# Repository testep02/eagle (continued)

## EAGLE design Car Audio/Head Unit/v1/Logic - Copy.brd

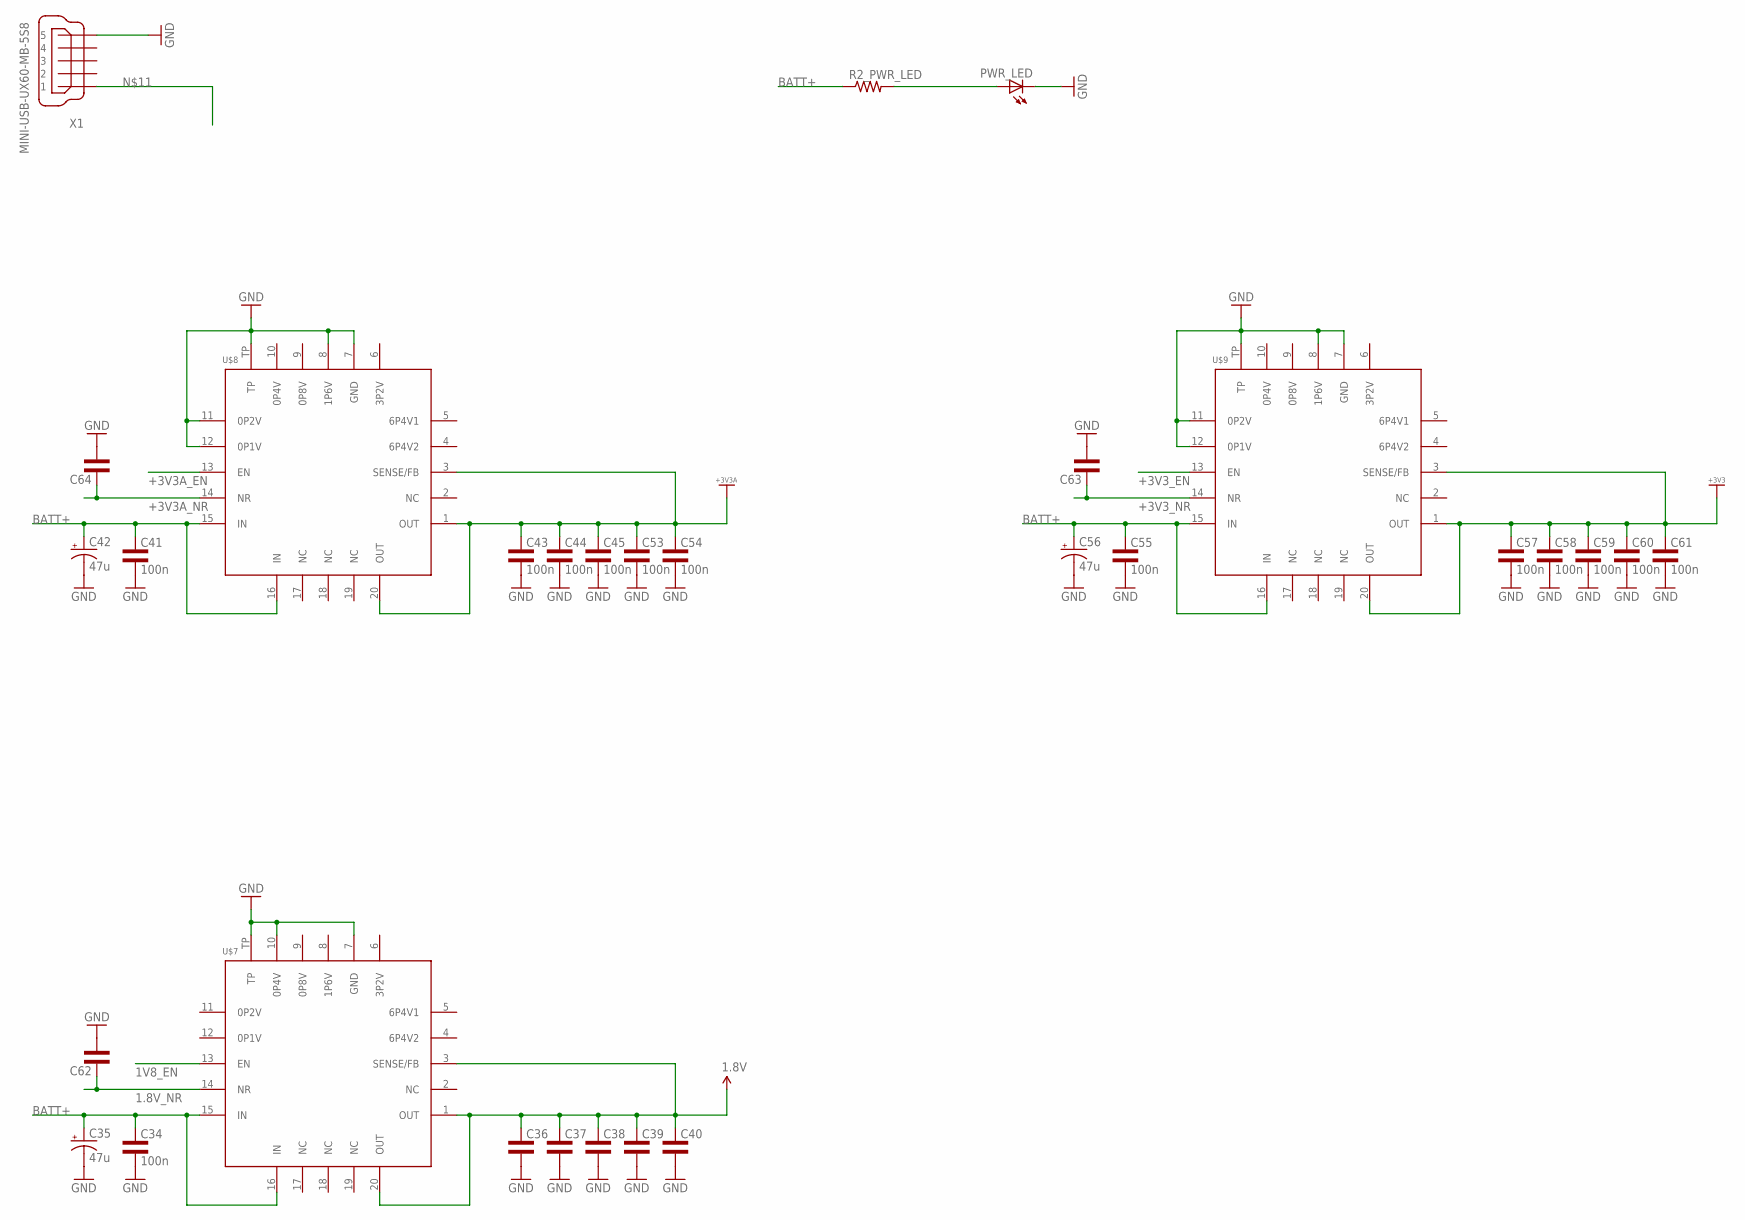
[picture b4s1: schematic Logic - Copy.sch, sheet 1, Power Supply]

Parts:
C34, C41, C43, C44, C45, C53, C54, C55, C57, C58, C59, C60, C61: 100n; 0805L3
C35, C42, C56: 47u; CT3528
C36, C37, C38, C39, C40: CAP0805L3; 0805L3
C62, C63, C64: CAP0402L3; 0402L3
PWR_LED: LEDCHIP-LED0603; CHIP-LED0603
R2_PWR_LED: RESISTOR0402-RES; 0402-RES
U$7, U$8, U$9: POWER-SUPPLY_POS_V1_TI_LDO_TPS7A4700; POWER-SUPPLY_POS_V1_TI_LDO_VQFN-20
X1: MINI-USB-UX60-MB-5S8; UX60-MB-5S8

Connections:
1.8V: C36.1, C37.1, C38.1, C39.1, C40.1, U$7.1 (OUT), U$7.3 (SENSE/FB), U$7.20 (OUT); also elsewhere on the board
1.8V_NR: C62.P$1 (1), U$7.14 (NR)
1V8_EN: U$7.13 (EN)
+3V3: C57.1, C58.1, C59.1, C60.1, C61.1, U$9.1 (OUT), U$9.3 (SENSE/FB), U$9.20 (OUT); also elsewhere on the board
+3V3A: C43.1, C44.1, C45.1, C53.1, C54.1, U$8.1 (OUT), U$8.3 (SENSE/FB), U$8.20 (OUT); also elsewhere on the board
+3V3A_EN: U$8.13 (EN)
+3V3A_NR: C64.P$1 (1), U$8.14 (NR)
+3V3_EN: U$9.13 (EN)
+3V3_NR: C63.P$1 (1), U$9.14 (NR)
BATT+: C34.1, C35.+, C41.1, C42.+, C55.1, C56.+, R2_PWR_LED.1, U$7.15 (IN), U$7.16 (IN), U$8.15 (IN), U$8.16 (IN), U$9.15 (IN), U$9.16 (IN)
GND: C34.2, C35.-, C36.2, C37.2, C38.2, C39.2, C40.2, C41.2, C42.-, C43.2, C44.2, C45.2, C53.2, C54.2, C55.2, C56.-, C57.2, C58.2, C59.2, C60.2, C61.2, C62.P$2 (2), C63.P$2 (2), C64.P$2 (2), PWR_LED.C, U$7.7 (GND), U$7.10 (0P4V), U$7.TP, U$8.7 (GND), U$8.8 (1P6V), U$8.11 (0P2V), U$8.12 (0P1V), U$8.TP, U$9.7 (GND), U$9.8 (1P6V), U$9.11 (0P2V), U$9.12 (0P1V), U$9.TP, X1.5; also elsewhere on the board
unnamed: PWR_LED.A, R2_PWR_LED.2

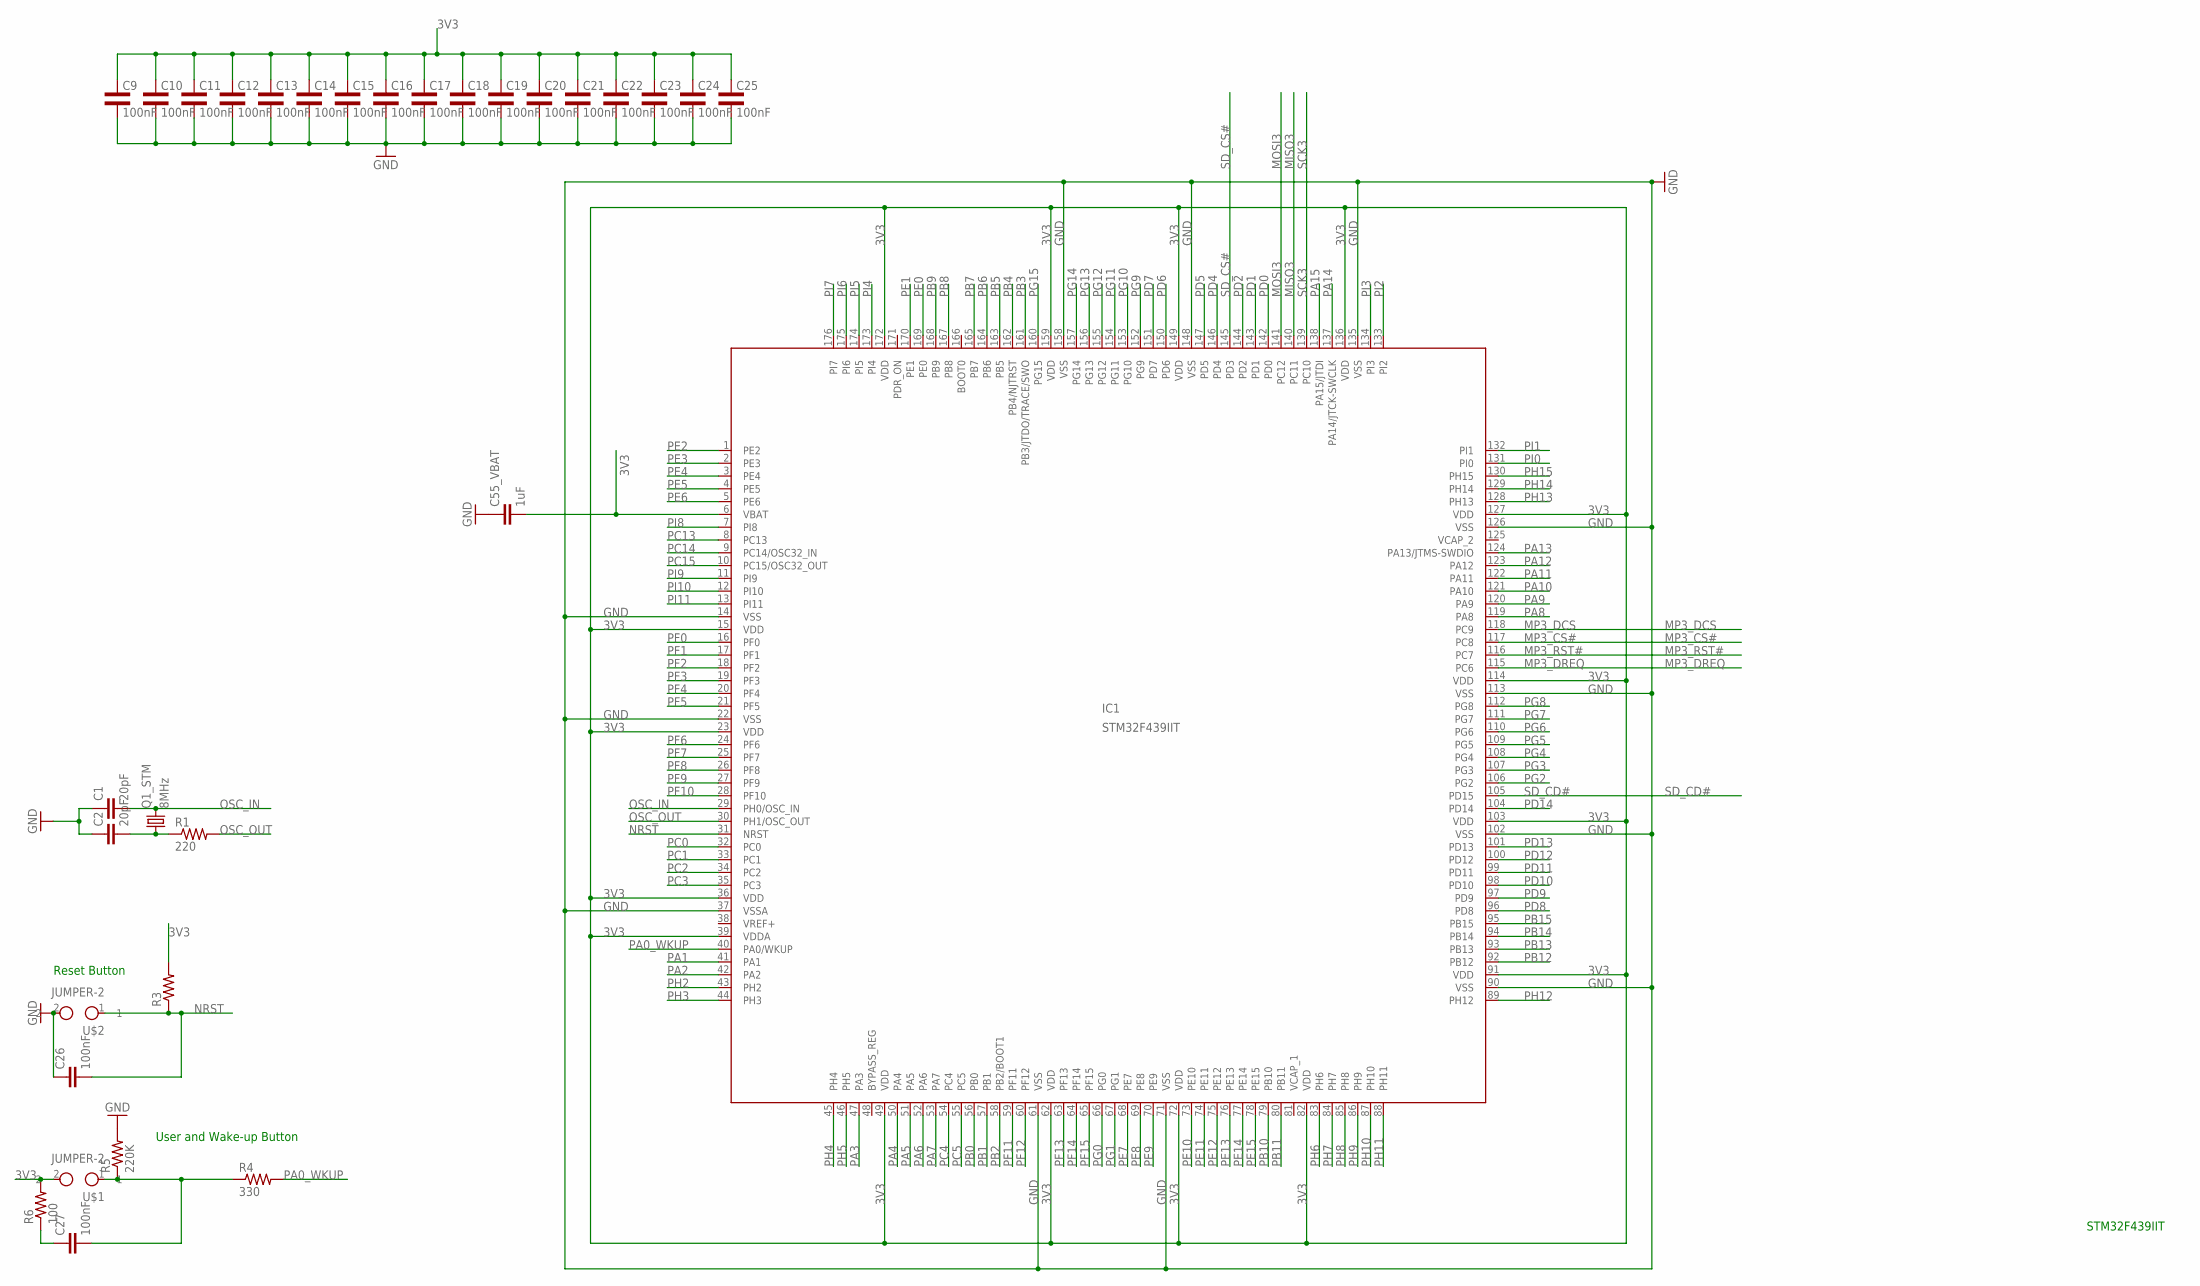
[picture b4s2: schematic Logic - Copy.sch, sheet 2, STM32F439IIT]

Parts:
C1, C2: 20pF; C0402
C9, C10, C11, C12, C13, C14, C15, C16, C17, C18, C19, C20, C21, C22, C23, C24, C25: 100nF; 0402L3
C26, C27: 100nF; C0402
C55_VBAT: 1uF; C0402
IC1: STM32F439IIT; LQFP-176
Q1_STM: 8MHz; CTS406
R1: 220; 0402-RES
R3: RESISTOR0402-RES; 0402-RES
R4: 330; 0402-RES
R5: 220K; 0402-RES
R6: 100; 0402-RES
U$1, U$2: JUMPER-2; 1X02

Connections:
3V3: C9.P$1 (1), C10.P$1 (1), C11.P$1 (1), C12.P$1 (1), C13.P$1 (1), C14.P$1 (1), C15.P$1 (1), C16.P$1 (1), C17.P$1 (1), C18.P$1 (1), C19.P$1 (1), C20.P$1 (1), C21.P$1 (1), C22.P$1 (1), C23.P$1 (1), C24.P$1 (1), C25.P$1 (1), C55_VBAT.2, IC1.6 (VBAT), IC1.15 (VDD), IC1.23 (VDD), IC1.36 (VDD), IC1.39 (VDDA), IC1.49 (VDD), IC1.62 (VDD), IC1.72 (VDD), IC1.82 (VDD), IC1.91 (VDD), IC1.103 (VDD), IC1.114 (VDD), IC1.127 (VDD), IC1.136 (VDD), IC1.149 (VDD), IC1.159 (VDD), IC1.172 (VDD), R3.2, R6.2, U$1.2; also elsewhere on the board
GND: C1.1, C2.1, C9.P$2 (2), C10.P$2 (2), C11.P$2 (2), C12.P$2 (2), C13.P$2 (2), C14.P$2 (2), C15.P$2 (2), C16.P$2 (2), C17.P$2 (2), C18.P$2 (2), C19.P$2 (2), C20.P$2 (2), C21.P$2 (2), C22.P$2 (2), C23.P$2 (2), C24.P$2 (2), C25.P$2 (2), C26.1, C55_VBAT.1, IC1.14 (VSS), IC1.22 (VSS), IC1.37 (VSSA), IC1.61 (VSS), IC1.71 (VSS), IC1.90 (VSS), IC1.102 (VSS), IC1.113 (VSS), IC1.126 (VSS), IC1.135 (VSS), IC1.148 (VSS), IC1.158 (VSS), R5.2, U$2.2; also elsewhere on the board
MISO3: IC1.140 (PC11); also elsewhere on the board
MOSI3: IC1.141 (PC12); also elsewhere on the board
MP3_CS#: IC1.117 (PC8); also elsewhere on the board
MP3_DCS: IC1.118 (PC9); also elsewhere on the board
MP3_DREQ: IC1.115 (PC6); also elsewhere on the board
MP3_RST#: IC1.116 (PC7); also elsewhere on the board
unnamed: C2.2, Q1_STM.1, R1.1
unnamed: C27.2, R4.1, R5.1, U$1.1
unnamed: C27.1, R6.1
NRST: C26.2, IC1.31 (NRST), R3.1, U$2.1
OSC_IN: C1.2, IC1.29 (PH0/OSC_IN), Q1_STM.3 (2)
OSC_OUT: IC1.30 (PH1/OSC_OUT), R1.2
PA0_WKUP: IC1.40 (PA0/WKUP), R4.2
PA1: IC1.41 (PA1)
PA2: IC1.42 (PA2)
PA3: IC1.47 (PA3)
PA4: IC1.50 (PA4)
PA5: IC1.51 (PA5)
PA6: IC1.52 (PA6)
PA7: IC1.53 (PA7)
PA8: IC1.119 (PA8)
PA9: IC1.120 (PA9)
PA10: IC1.121 (PA10)
PA11: IC1.122 (PA11)
PA12: IC1.123 (PA12)
PA13: IC1.124 (PA13/JTMS-SWDIO)
PA14: IC1.137 (PA14/JTCK-SWCLK)
PA15: IC1.138 (PA15/JTDI)
PB0: IC1.56 (PB0)
PB1: IC1.57 (PB1)
PB2: IC1.58 (PB2/BOOT1)
PB3: IC1.161 (PB3/JTDO/TRACE/SWO)
PB4: IC1.162 (PB4/NJTRST)
PB5: IC1.163 (PB5); also elsewhere on the board
PB6: IC1.164 (PB6); also elsewhere on the board
PB7: IC1.165 (PB7)
PB8: IC1.167 (PB8)
PB9: IC1.168 (PB9)
PB10: IC1.79 (PB10)
PB11: IC1.80 (PB11)
PB12: IC1.92 (PB12)
PB13: IC1.93 (PB13)
PB14: IC1.94 (PB14)
PB15: IC1.95 (PB15)
PC0: IC1.32 (PC0); also elsewhere on the board
PC1: IC1.33 (PC1)
PC2: IC1.34 (PC2)
PC3: IC1.35 (PC3)
PC4: IC1.54 (PC4)
PC5: IC1.55 (PC5)
PC13: IC1.8 (PC13)
PC14: IC1.9 (PC14/OSC32_IN)
PC15: IC1.10 (PC15/OSC32_OUT)
PD0: IC1.142 (PD0); also elsewhere on the board
PD1: IC1.143 (PD1); also elsewhere on the board
PD2: IC1.144 (PD2)
PD4: IC1.146 (PD4)
PD5: IC1.147 (PD5)
PD6: IC1.150 (PD6)
PD7: IC1.151 (PD7)
PD8: IC1.96 (PD8); also elsewhere on the board
PD9: IC1.97 (PD9); also elsewhere on the board
PD10: IC1.98 (PD10); also elsewhere on the board
PD11: IC1.99 (PD11)
PD12: IC1.100 (PD12)
PD13: IC1.101 (PD13)
PD14: IC1.104 (PD14); also elsewhere on the board
PDR_ON: IC1.171 (PDR_ON)
PE0: IC1.169 (PE0); also elsewhere on the board
PE1: IC1.170 (PE1); also elsewhere on the board
PE2: IC1.1 (PE2)
PE3: IC1.2 (PE3)
PE4: IC1.3 (PE4)
PE5: IC1.4 (PE5)
PE6: IC1.5 (PE6)
PE7: IC1.68 (PE7); also elsewhere on the board
PE8: IC1.69 (PE8); also elsewhere on the board
PE9: IC1.70 (PE9); also elsewhere on the board
PE10: IC1.73 (PE10); also elsewhere on the board
PE11: IC1.74 (PE11); also elsewhere on the board
PE12: IC1.75 (PE12); also elsewhere on the board
PE13: IC1.76 (PE13); also elsewhere on the board
PE14: IC1.77 (PE14); also elsewhere on the board
PE15: IC1.78 (PE15); also elsewhere on the board
PF0: IC1.16 (PF0); also elsewhere on the board
PF1: IC1.17 (PF1); also elsewhere on the board
PF2: IC1.18 (PF2); also elsewhere on the board
PF3: IC1.19 (PF3); also elsewhere on the board
PF4: IC1.20 (PF4); also elsewhere on the board
PF5: IC1.21 (PF5); also elsewhere on the board
PF6: IC1.24 (PF6)
PF7: IC1.25 (PF7)
PF8: IC1.26 (PF8)
PF9: IC1.27 (PF9)
PF10: IC1.28 (PF10)
PF11: IC1.59 (PF11); also elsewhere on the board
PF12: IC1.60 (PF12); also elsewhere on the board
PF13: IC1.63 (PF13); also elsewhere on the board
PF14: IC1.64 (PF14); also elsewhere on the board
PF15: IC1.65 (PF15); also elsewhere on the board
PG0: IC1.66 (PG0); also elsewhere on the board
PG1: IC1.67 (PG1); also elsewhere on the board
PG2: IC1.106 (PG2)
PG3: IC1.107 (PG3)
PG4: IC1.108 (PG4); also elsewhere on the board
PG5: IC1.109 (PG5); also elsewhere on the board
PG6: IC1.110 (PG6)
PG7: IC1.111 (PG7)
PG8: IC1.112 (PG8); also elsewhere on the board
PG9: IC1.152 (PG9)
PG10: IC1.153 (PG10)
PG11: IC1.154 (PG11)
PG12: IC1.155 (PG12)
PG13: IC1.156 (PG13)
PG14: IC1.157 (PG14)
PG15: IC1.160 (PG15); also elsewhere on the board
PH2: IC1.43 (PH2)
PH3: IC1.44 (PH3)
PH4: IC1.45 (PH4)
PH5: IC1.46 (PH5)
PH6: IC1.83 (PH6)
PH7: IC1.84 (PH7)
PH8: IC1.85 (PH8)
PH9: IC1.86 (PH9)
PH10: IC1.87 (PH10)
PH11: IC1.88 (PH11)
PH12: IC1.89 (PH12)
PH13: IC1.128 (PH13)
PH14: IC1.129 (PH14)
PH15: IC1.130 (PH15)
PI0: IC1.131 (PI0)
PI1: IC1.132 (PI1)
PI2: IC1.133 (PI2)
PI3: IC1.134 (PI3)
PI4: IC1.173 (PI4)
PI5: IC1.174 (PI5)
PI6: IC1.175 (PI6)
PI7: IC1.176 (PI7)
PI8: IC1.7 (PI8)
PI9: IC1.11 (PI9)
PI10: IC1.12 (PI10)
PI11: IC1.13 (PI11)
SCK3: IC1.139 (PC10); also elsewhere on the board
SD_CD#: IC1.105 (PD15)
SD_CS#: IC1.145 (PD3)
VCAP_1: IC1.81 (VCAP_1)
VCAP_2: IC1.125 (VCAP_2)
VREF+: IC1.38 (VREF+)

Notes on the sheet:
STM32F439IIT
Reset Button
User and Wake-up Button

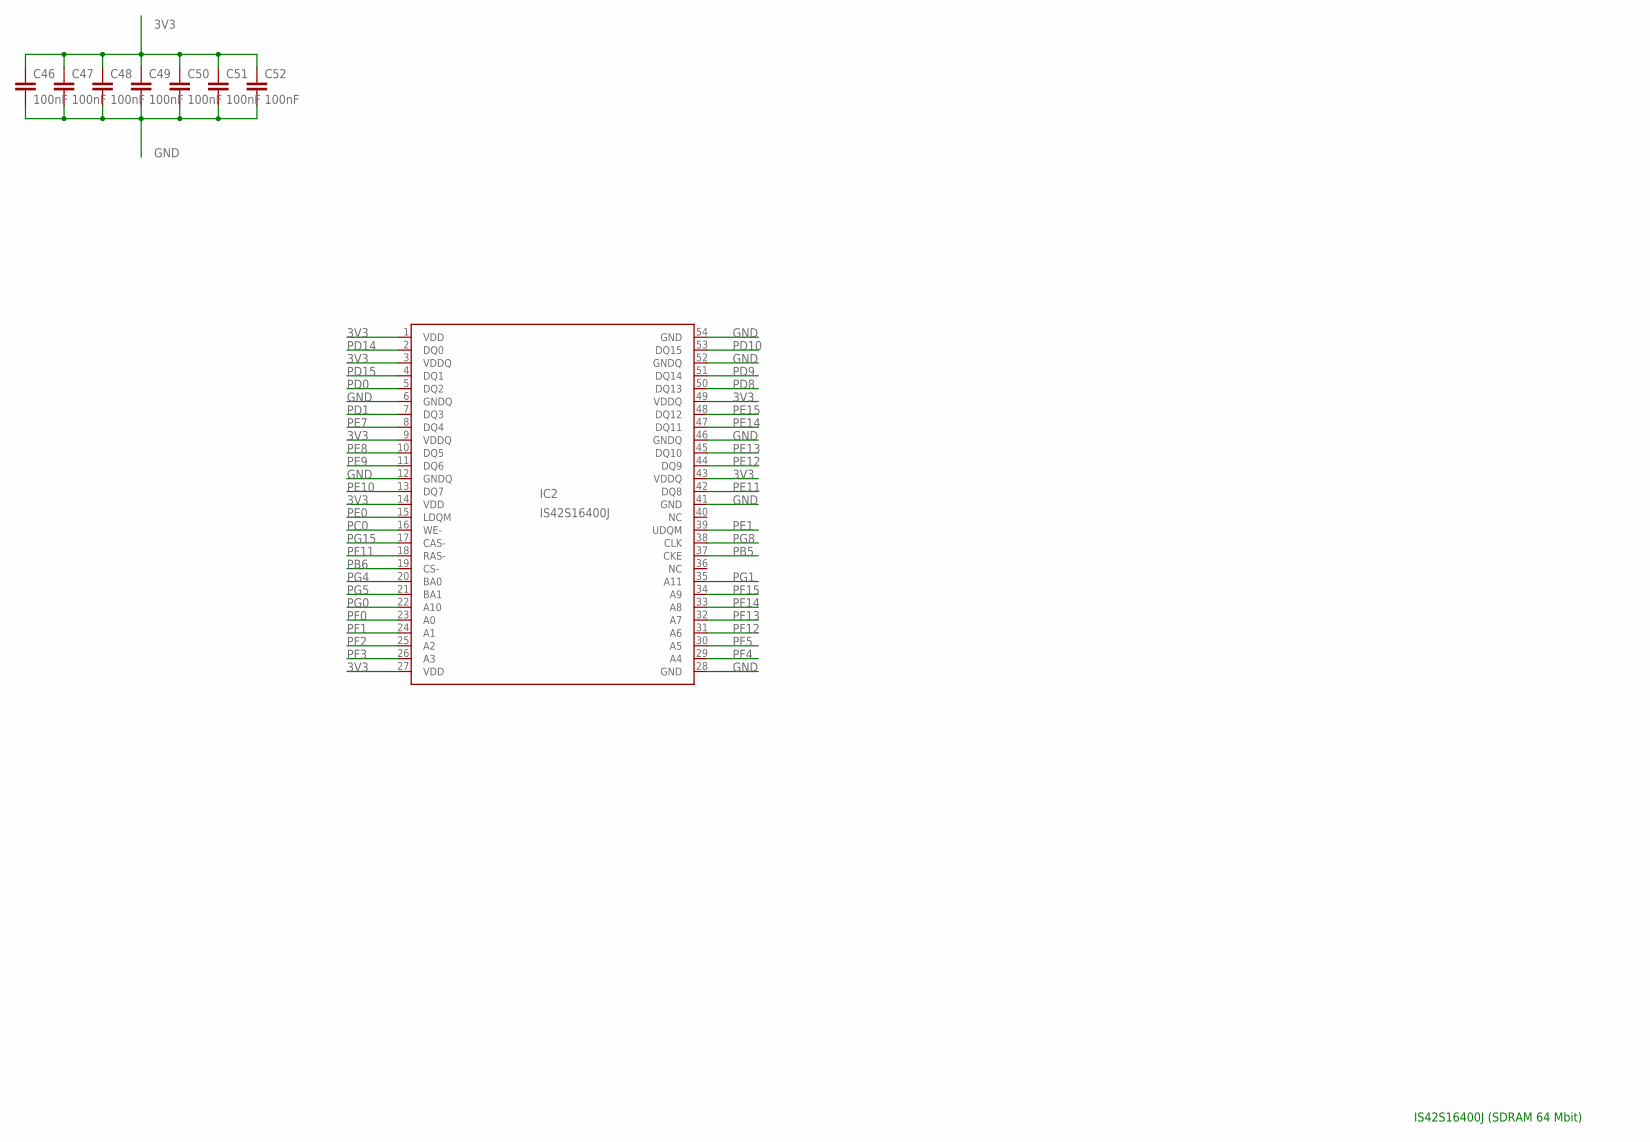
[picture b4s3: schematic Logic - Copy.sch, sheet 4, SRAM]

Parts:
C46, C47, C48, C49, C50, C51, C52: 100nF; C0402
IC2: IS42S16400J; TSOP-2

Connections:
3V3: C46.1, C47.1, C48.1, C49.1, C50.1, C51.1, C52.1, IC2.1 (VDD), IC2.3 (VDDQ), IC2.9 (VDDQ), IC2.14 (VDD), IC2.27 (VDD), IC2.43 (VDDQ), IC2.49 (VDDQ); also elsewhere on the board
GND: C46.2, C47.2, C48.2, C49.2, C50.2, C51.2, C52.2, IC2.6 (GNDQ), IC2.12 (GNDQ), IC2.28 (GND), IC2.41 (GND), IC2.46 (GNDQ), IC2.52 (GNDQ), IC2.54 (GND); also elsewhere on the board
PB5: IC2.37 (CKE); also elsewhere on the board
PB6: IC2.19 (CS-); also elsewhere on the board
PC0: IC2.16 (WE-); also elsewhere on the board
PD0: IC2.5 (DQ2); also elsewhere on the board
PD1: IC2.7 (DQ3); also elsewhere on the board
PD8: IC2.50 (DQ13); also elsewhere on the board
PD9: IC2.51 (DQ14); also elsewhere on the board
PD10: IC2.53 (DQ15); also elsewhere on the board
PD14: IC2.2 (DQ0); also elsewhere on the board
PD15: IC2.4 (DQ1)
PE0: IC2.15 (LDQM); also elsewhere on the board
PE1: IC2.39 (UDQM); also elsewhere on the board
PE7: IC2.8 (DQ4); also elsewhere on the board
PE8: IC2.10 (DQ5); also elsewhere on the board
PE9: IC2.11 (DQ6); also elsewhere on the board
PE10: IC2.13 (DQ7); also elsewhere on the board
PE11: IC2.42 (DQ8); also elsewhere on the board
PE12: IC2.44 (DQ9); also elsewhere on the board
PE13: IC2.45 (DQ10); also elsewhere on the board
PE14: IC2.47 (DQ11); also elsewhere on the board
PE15: IC2.48 (DQ12); also elsewhere on the board
PF0: IC2.23 (A0); also elsewhere on the board
PF1: IC2.24 (A1); also elsewhere on the board
PF2: IC2.25 (A2); also elsewhere on the board
PF3: IC2.26 (A3); also elsewhere on the board
PF4: IC2.29 (A4); also elsewhere on the board
PF5: IC2.30 (A5); also elsewhere on the board
PF11: IC2.18 (RAS-); also elsewhere on the board
PF12: IC2.31 (A6); also elsewhere on the board
PF13: IC2.32 (A7); also elsewhere on the board
PF14: IC2.33 (A8); also elsewhere on the board
PF15: IC2.34 (A9); also elsewhere on the board
PG0: IC2.22 (A10); also elsewhere on the board
PG1: IC2.35 (A11); also elsewhere on the board
PG4: IC2.20 (BA0); also elsewhere on the board
PG5: IC2.21 (BA1); also elsewhere on the board
PG8: IC2.38 (CLK); also elsewhere on the board
PG15: IC2.17 (CAS-); also elsewhere on the board

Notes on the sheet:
IS42S16400J (SDRAM 64 Mbit)

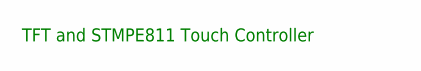
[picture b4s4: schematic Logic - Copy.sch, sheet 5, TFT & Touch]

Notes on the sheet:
TFT and STMPE811 Touch Controller

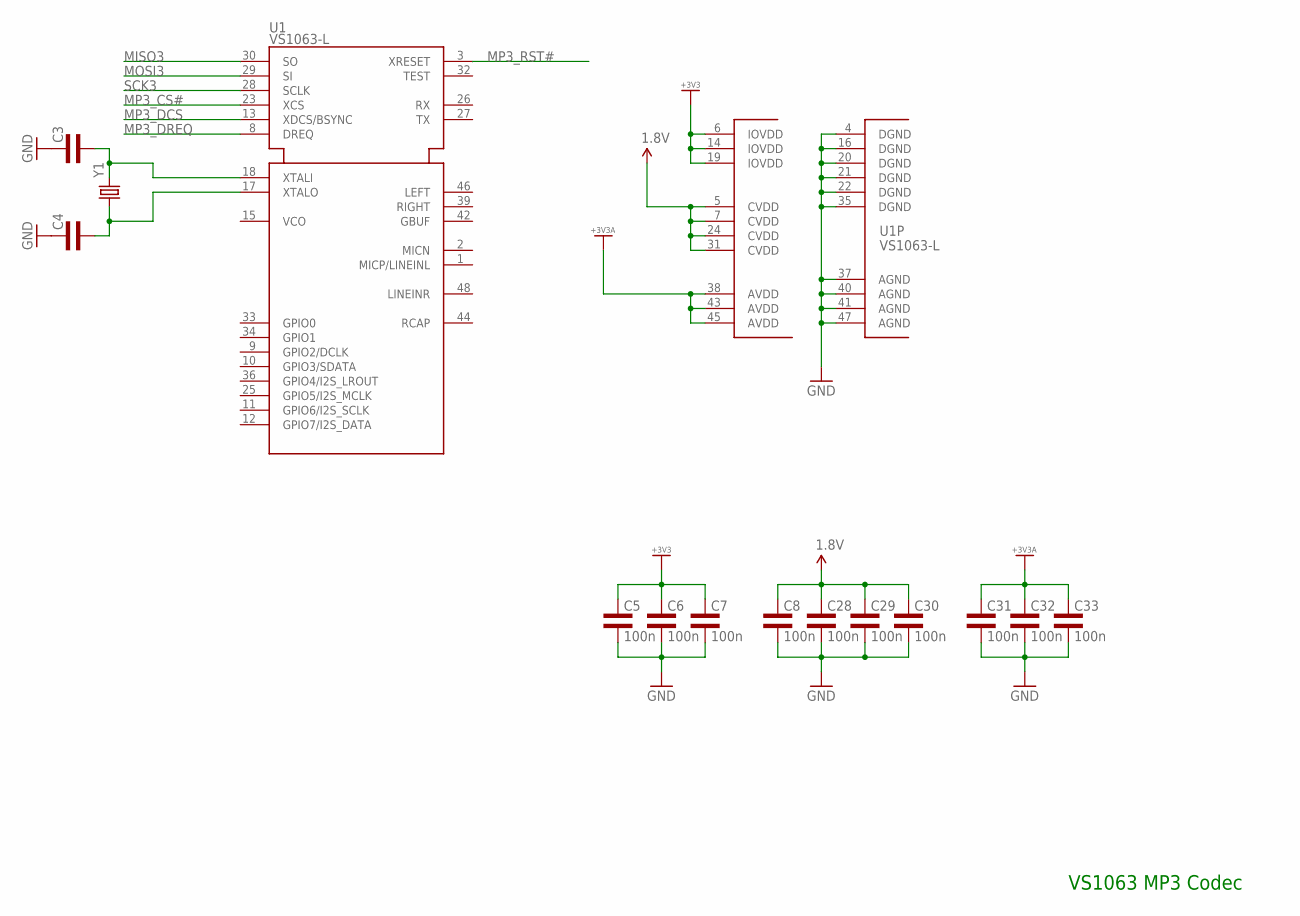
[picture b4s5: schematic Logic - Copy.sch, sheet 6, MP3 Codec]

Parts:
C3, C4: CAP0603L3; 0603L3
C5, C6, C7, C8, C28, C29, C30, C31, C32, C33: 100n; 0402L3
U1: VS1063-L; LQFP48
Y1: CRYSTALHC49US; HC49US

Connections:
1.8V: C8.P$1 (1), C28.P$1 (1), C29.P$1 (1), C30.P$1 (1), U1.5 (CVDD), U1.7 (CVDD), U1.24 (CVDD), U1.31 (CVDD); also elsewhere on the board
+3V3: C5.P$1 (1), C6.P$1 (1), C7.P$1 (1), U1.6 (IOVDD), U1.14 (IOVDD), U1.19 (IOVDD); also elsewhere on the board
+3V3A: C31.P$1 (1), C32.P$1 (1), C33.P$1 (1), U1.38 (AVDD), U1.43 (AVDD), U1.45 (AVDD); also elsewhere on the board
GND: C3.P$1 (1), C4.P$1 (1), C5.P$2 (2), C6.P$2 (2), C7.P$2 (2), C8.P$2 (2), C28.P$2 (2), C29.P$2 (2), C30.P$2 (2), C31.P$2 (2), C32.P$2 (2), C33.P$2 (2), U1.4 (DGND), U1.16 (DGND), U1.20 (DGND), U1.21 (DGND), U1.22 (DGND), U1.35 (DGND), U1.37 (AGND), U1.40 (AGND), U1.41 (AGND), U1.47 (AGND); also elsewhere on the board
MISO3: U1.30 (SO); also elsewhere on the board
MOSI3: U1.29 (SI); also elsewhere on the board
MP3_CS#: U1.23 (XCS); also elsewhere on the board
MP3_DCS: U1.13 (XDCS/BSYNC); also elsewhere on the board
MP3_DREQ: U1.8 (DREQ); also elsewhere on the board
MP3_RST#: U1.3 (XRESET); also elsewhere on the board
unnamed: C3.P$2 (2), U1.18 (XTALI), Y1.2
unnamed: C4.P$2 (2), U1.17 (XTALO), Y1.1
SCK3: U1.28 (SCLK); also elsewhere on the board

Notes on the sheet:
VS1063 MP3 Codec

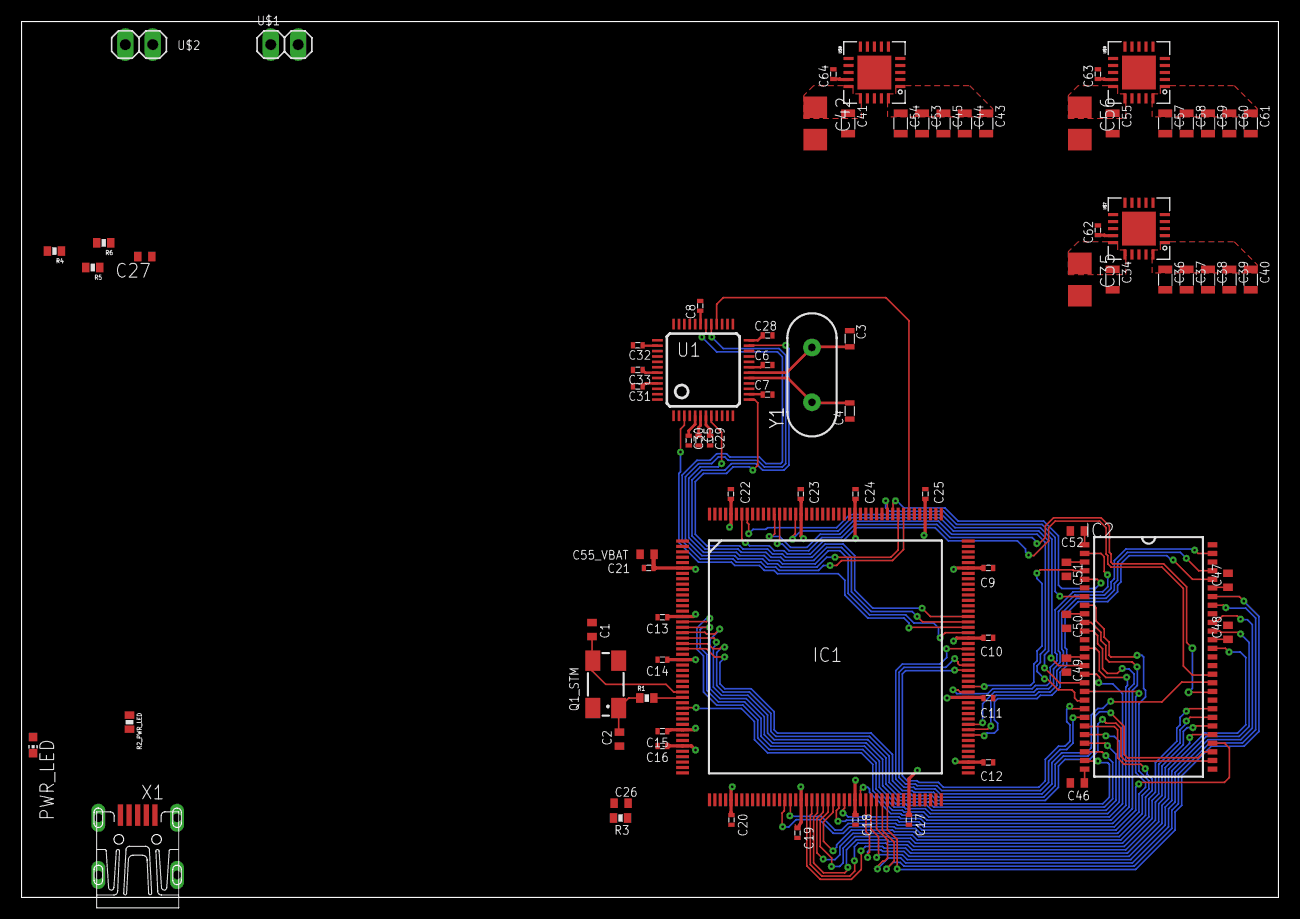
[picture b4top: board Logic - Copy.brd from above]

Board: 4 copper layers, 116.6 x 81.2 mm, 83 parts (0 on the bottom side), 63 nets.

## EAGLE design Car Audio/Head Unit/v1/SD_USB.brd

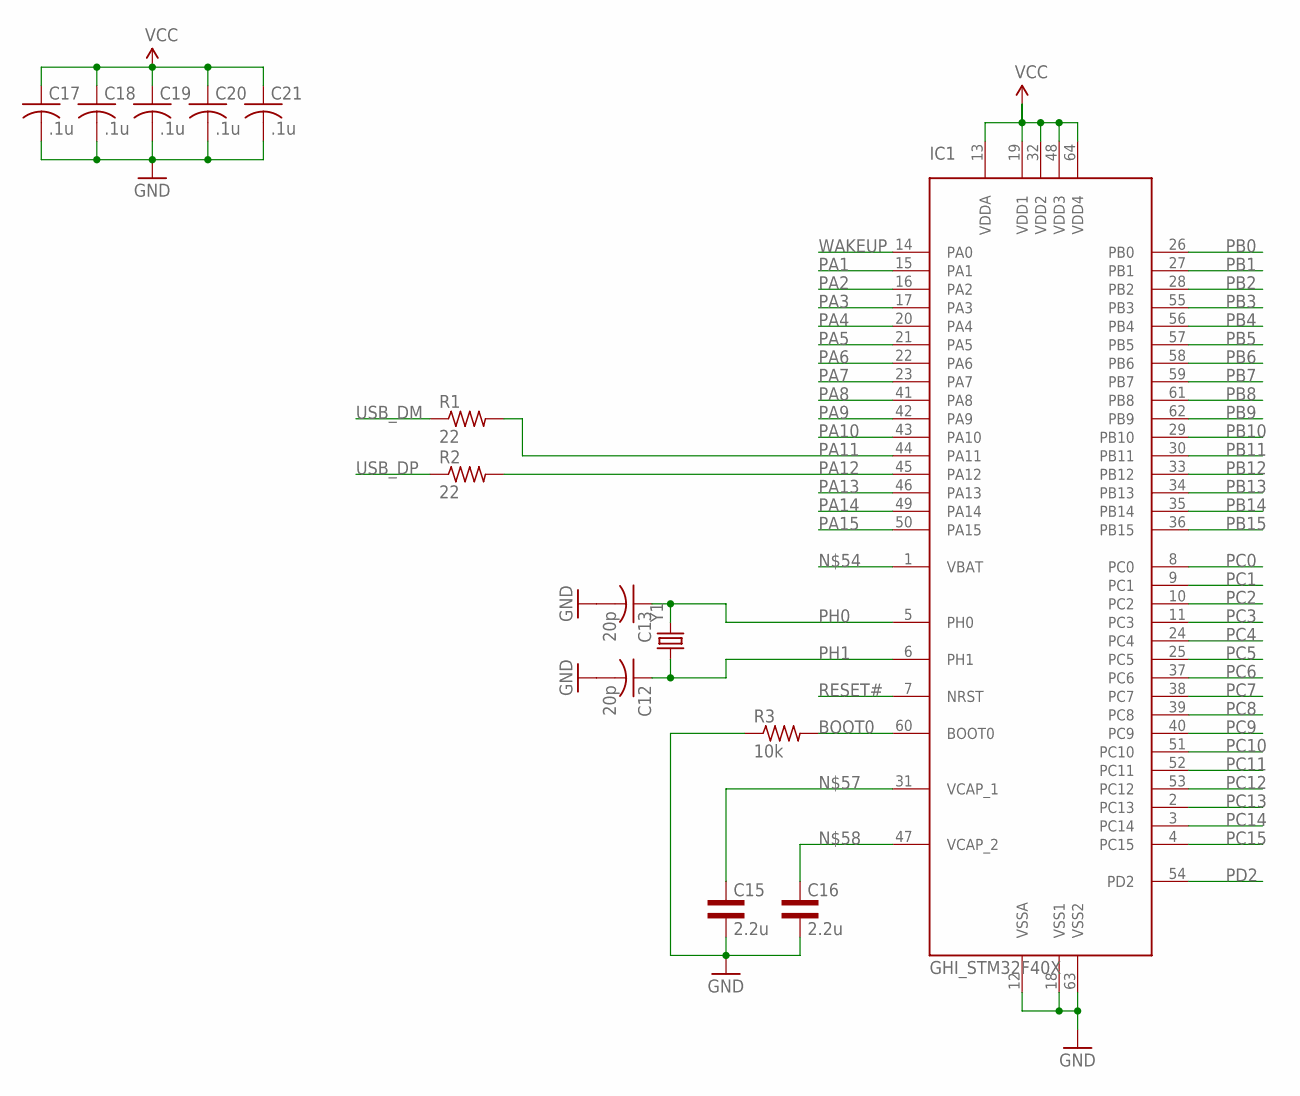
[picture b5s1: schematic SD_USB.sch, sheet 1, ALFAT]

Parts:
C12, C13: 20p; C0603
C15, C16: 2.2u; 0805L3
C17, C18, C19, C20, C21: .1u; C0603
IC1: GHI_STM32F40X; GHI_LQFP64
R1, R2: 22; R0603
R3: 10k; R0603
Y1: CRYSTALHC49US; HC49US

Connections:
BOOT0: IC1.60 (BOOT0), R3.2
GND: C12.2, C13.2, C15.2, C16.2, C17.2, C18.2, C19.2, C20.2, C21.2, IC1.12 (VSSA), IC1.18 (VSS1), IC1.63 (VSS2), R3.1
unnamed: C15.1, IC1.31 (VCAP_1)
unnamed: C16.1, IC1.47 (VCAP_2)
PA1: IC1.15 (PA1)
PA2: IC1.16 (PA2)
PA3: IC1.17 (PA3); also elsewhere on the board
PA4: IC1.20 (PA4)
PA5: IC1.21 (PA5); also elsewhere on the board
PA6: IC1.22 (PA6)
PA7: IC1.23 (PA7)
PA8: IC1.41 (PA8); also elsewhere on the board
PA9: IC1.42 (PA9)
PA10: IC1.43 (PA10)
PA11: IC1.44 (PA11), R1.2
PA12: IC1.45 (PA12), R2.2
PA13: IC1.46 (PA13)
PA14: IC1.49 (PA14)
PA15: IC1.50 (PA15)
PB0: IC1.26 (PB0); also elsewhere on the board
PB1: IC1.27 (PB1); also elsewhere on the board
PB2: IC1.28 (PB2)
PB3: IC1.55 (PB3)
PB4: IC1.56 (PB4)
PB5: IC1.57 (PB5); also elsewhere on the board
PB6: IC1.58 (PB6)
PB7: IC1.59 (PB7)
PB8: IC1.61 (PB8)
PB9: IC1.62 (PB9)
PB10: IC1.29 (PB10); also elsewhere on the board
PB11: IC1.30 (PB11); also elsewhere on the board
PB12: IC1.33 (PB12); also elsewhere on the board
PB13: IC1.34 (PB13); also elsewhere on the board
PB14: IC1.35 (PB14)
PB15: IC1.36 (PB15)
PC0: IC1.8 (PC0); also elsewhere on the board
PC1: IC1.9 (PC1)
PC2: IC1.10 (PC2); also elsewhere on the board
PC3: IC1.11 (PC3); also elsewhere on the board
PC4: IC1.24 (PC4); also elsewhere on the board
PC5: IC1.25 (PC5); also elsewhere on the board
PC6: IC1.37 (PC6)
PC7: IC1.38 (PC7)
PC8: IC1.39 (PC8); also elsewhere on the board
PC9: IC1.40 (PC9); also elsewhere on the board
PC10: IC1.51 (PC10); also elsewhere on the board
PC11: IC1.52 (PC11); also elsewhere on the board
PC12: IC1.53 (PC12); also elsewhere on the board
PC13: IC1.2 (PC13)
PC14: IC1.3 (PC14)
PC15: IC1.4 (PC15)
PD2: IC1.54 (PD2); also elsewhere on the board
PH0: C13.1, IC1.5 (PH0), Y1.2
PH1: C12.1, IC1.6 (PH1), Y1.1
RESET#: IC1.7 (NRST)
USB_DM: R1.1; also elsewhere on the board
USB_DP: R2.1; also elsewhere on the board
VCC: C17.1, C18.1, C19.1, C20.1, C21.1, IC1.13 (VDDA), IC1.19 (VDD1), IC1.32 (VDD2), IC1.48 (VDD3), IC1.64 (VDD4)
WAKEUP: IC1.14 (PA0)

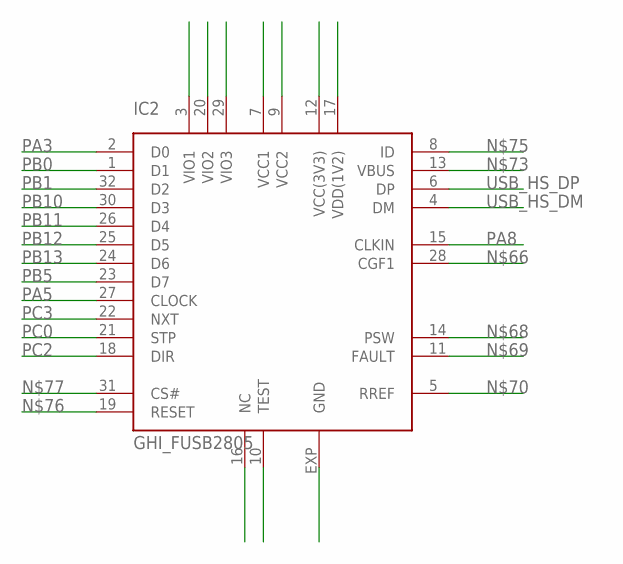
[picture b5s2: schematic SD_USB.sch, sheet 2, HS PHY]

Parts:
IC2: GHI_FUSB2805; GHI_MLP32

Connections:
PA3: IC2.2 (D0); also elsewhere on the board
PA5: IC2.27 (CLOCK); also elsewhere on the board
PA8: IC2.15 (CLKIN); also elsewhere on the board
PB0: IC2.1 (D1); also elsewhere on the board
PB1: IC2.32 (D2); also elsewhere on the board
PB5: IC2.23 (D7); also elsewhere on the board
PB10: IC2.30 (D3); also elsewhere on the board
PB11: IC2.26 (D4); also elsewhere on the board
PB12: IC2.25 (D5); also elsewhere on the board
PB13: IC2.24 (D6); also elsewhere on the board
PC0: IC2.21 (STP); also elsewhere on the board
PC2: IC2.18 (DIR); also elsewhere on the board
PC3: IC2.22 (NXT); also elsewhere on the board
USB_HS_DM: IC2.4 (DM); also elsewhere on the board
USB_HS_DP: IC2.6 (DP); also elsewhere on the board

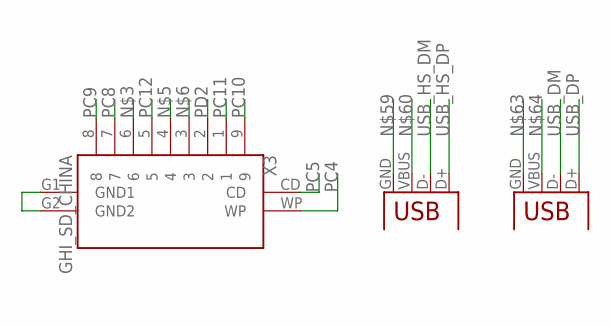
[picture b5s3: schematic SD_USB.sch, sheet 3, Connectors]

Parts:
X1, X2: USB-A-H
X3: GHI_SD_CHINA

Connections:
unnamed: X3.G1 (GND1), X3.G2 (GND2)
PC4: X3.WP; also elsewhere on the board
PC5: X3.CD; also elsewhere on the board
PC8: X3.7; also elsewhere on the board
PC9: X3.8; also elsewhere on the board
PC10: X3.9; also elsewhere on the board
PC11: X3.1; also elsewhere on the board
PC12: X3.5; also elsewhere on the board
PD2: X3.2; also elsewhere on the board
USB_DM: X2.D-; also elsewhere on the board
USB_DP: X2.D+; also elsewhere on the board
USB_HS_DM: X1.D-; also elsewhere on the board
USB_HS_DP: X1.D+; also elsewhere on the board

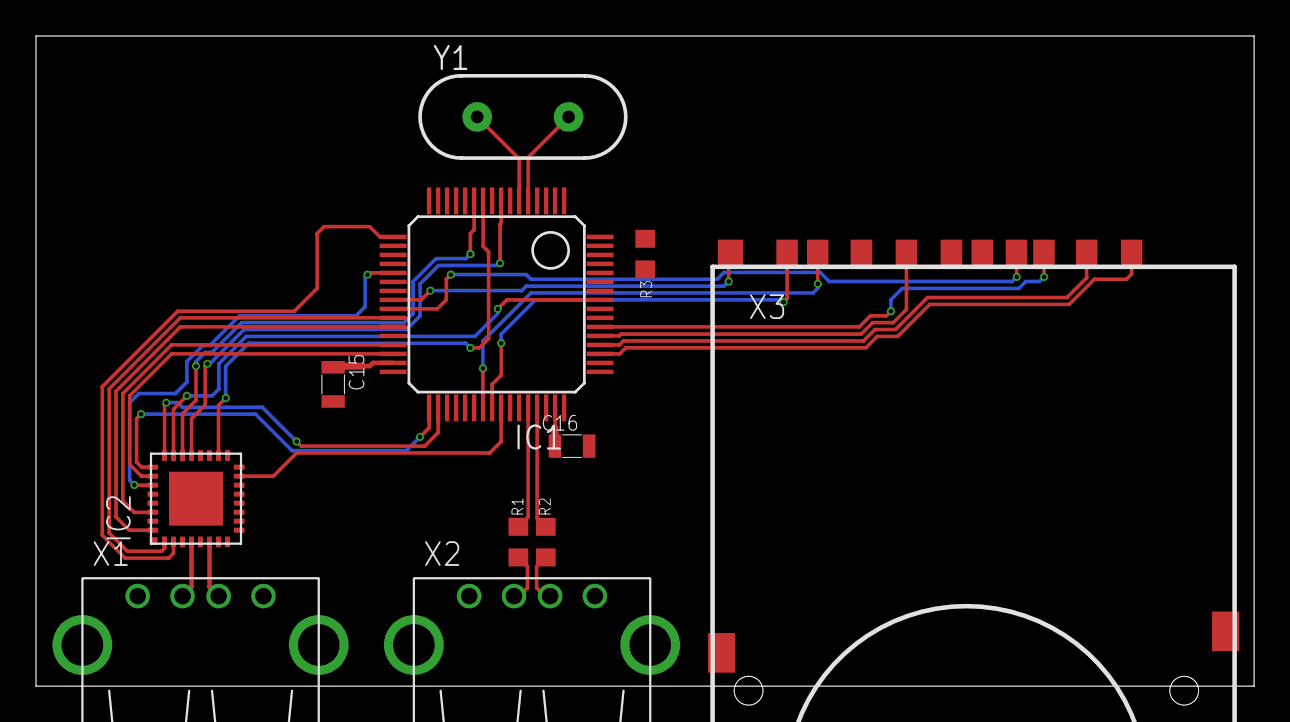
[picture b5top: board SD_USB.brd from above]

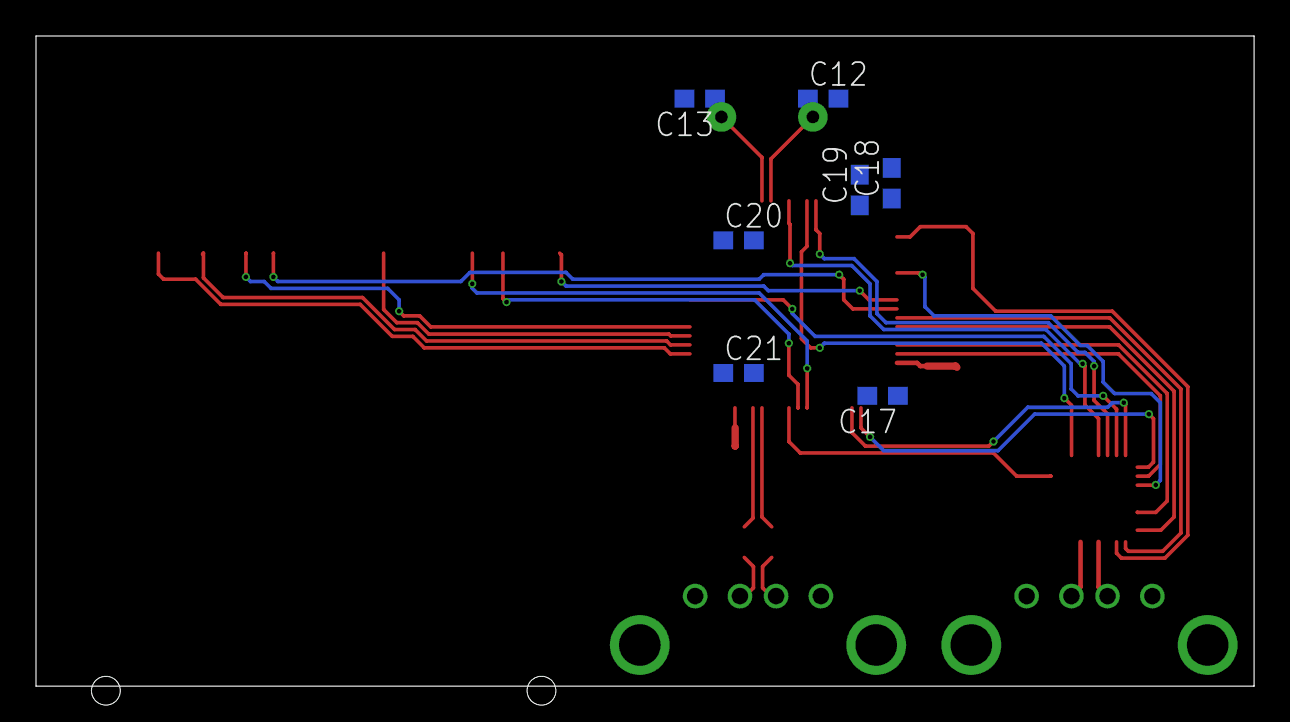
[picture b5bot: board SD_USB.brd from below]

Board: 4 copper layers, 67.7 x 36.1 mm, 18 parts (7 on the bottom side), 35 nets.

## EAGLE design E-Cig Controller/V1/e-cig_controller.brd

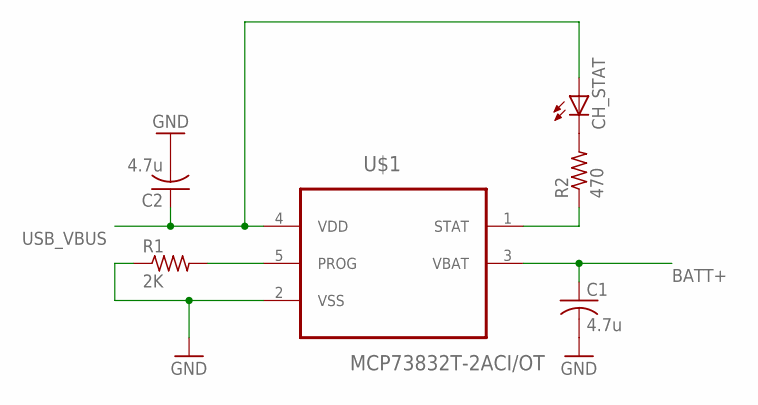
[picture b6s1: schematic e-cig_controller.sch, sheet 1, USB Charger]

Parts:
C1, C2: 4.7u; C0603
CH_STAT: LEDCHIP-LED0603; CHIP-LED0603
R1: 2K; R0603
R2: 470; R0603
U$1: MCP73832T-2ACI/OT; SOT95P280X145-5N

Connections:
BATT+: C1.1, U$1.3 (VBAT); also elsewhere on the board
GND: C1.2, C2.2, R1.1, U$1.2 (VSS); also elsewhere on the board
unnamed: R1.2, U$1.5 (PROG)
unnamed: CH_STAT.C, R2.2
unnamed: R2.1, U$1.1 (STAT)
USB_VBUS: C2.1, CH_STAT.A, U$1.4 (VDD)
